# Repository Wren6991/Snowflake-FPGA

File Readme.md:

Snowflake FPGA HAT
==================

As an experiment, I am designing a PCB using only my Pi 4 4GB. Any other machine is off-limits. This includes

- Schematic entry
- Layout
- Datasheets and reference material
- Background Twitter browsing
- Rendering PCB glamour shots:

This is a HAT (Raspberry Pi addon board) with an iCE40 HX8k FPGA. The Pi can program the FPGA, and communicate with it via a UART, or a fast, bidirectional SDIO link. This project was spurred by the realisation that Pi 4 is a plausible FPGA development platform: faster processors, expanded memory and, above all, dramatic improvements in [Symbiotic EDA](https://www.symbioticeda.com/)'s open source design flows in the last few years.

[View schematic (PDF)](board/fpga_hat.pdf)

With the exception of the `datasheet/` directory (to which I do not lay claim), this repository is distributed under the [Apache-2.0 License](License).

Features
--------

- iCE40 HX8k
- 4 Mbit SRAM 16 bit wide, 10 ns access
- 4 Mbit flash for FPGA image and user data; dual I/O support
- 3 PMOD-compatible expansion headers
    - 8 3.3V IOs each, plus power and ground
    - 2 headers on one side, 1 on another; the two on one side have standard 0.9" spacing, allowing use of dual-PMOD boards
- Communication with host Pi:
    - UART
    - SPI for flash programming
    - SDIO for fast communications
    - FPGA reset, and configuration status (CDONE)
- 8 user pushbuttons and LEDs
- Reset button and configuration status LED
- Audio output via 3.5 mm jack (same audio circuit as Pi)

Tolerances
----------

Of the 121 balls on the FPGA's BGA package, I am using 120; the sole unconnected ball is VPP_FAST, which is used only for NVCM programming. This will make the layout exceptionally tight, which is part of the experiment! For a fighting chance, I am using JLCPCB to manufacture the prototype boards, rather than my usual iTead. Their tighter manufacturing tolerances should permit two traces between 0.3 mm pads on a 0.8 mm-pitch BGA, which allows the first 3 ranks of balls to be routed out on layer 1.

The capability requirements for this board are:

- Via drill 0.2 mm
- Via diameter 0.45 mm
- Copper min width 0.09 mm
- Copper-copper clearance 0.09 mm
- Solder mask expansion 0.05 mm

Stackup
-------

This is a 4-layer board.

- L1: signal, GND fill
- L2: GND plane
- L3: Power polygons (+5V, +3V3, +1V2)
- L4: signal, GND fill

All layers 1 oz/sqft copper. Assumed stacking for FR4 layers:

- L1-L2 0.2 mm prepreg
- L2-L3 1.2 mm core
- L3-L4 0.2 mm prepreg

These dimensions are not critical. Signal integrity will be improved by minimising separation of L1-L2, but none of the routing is impedance-controlled.

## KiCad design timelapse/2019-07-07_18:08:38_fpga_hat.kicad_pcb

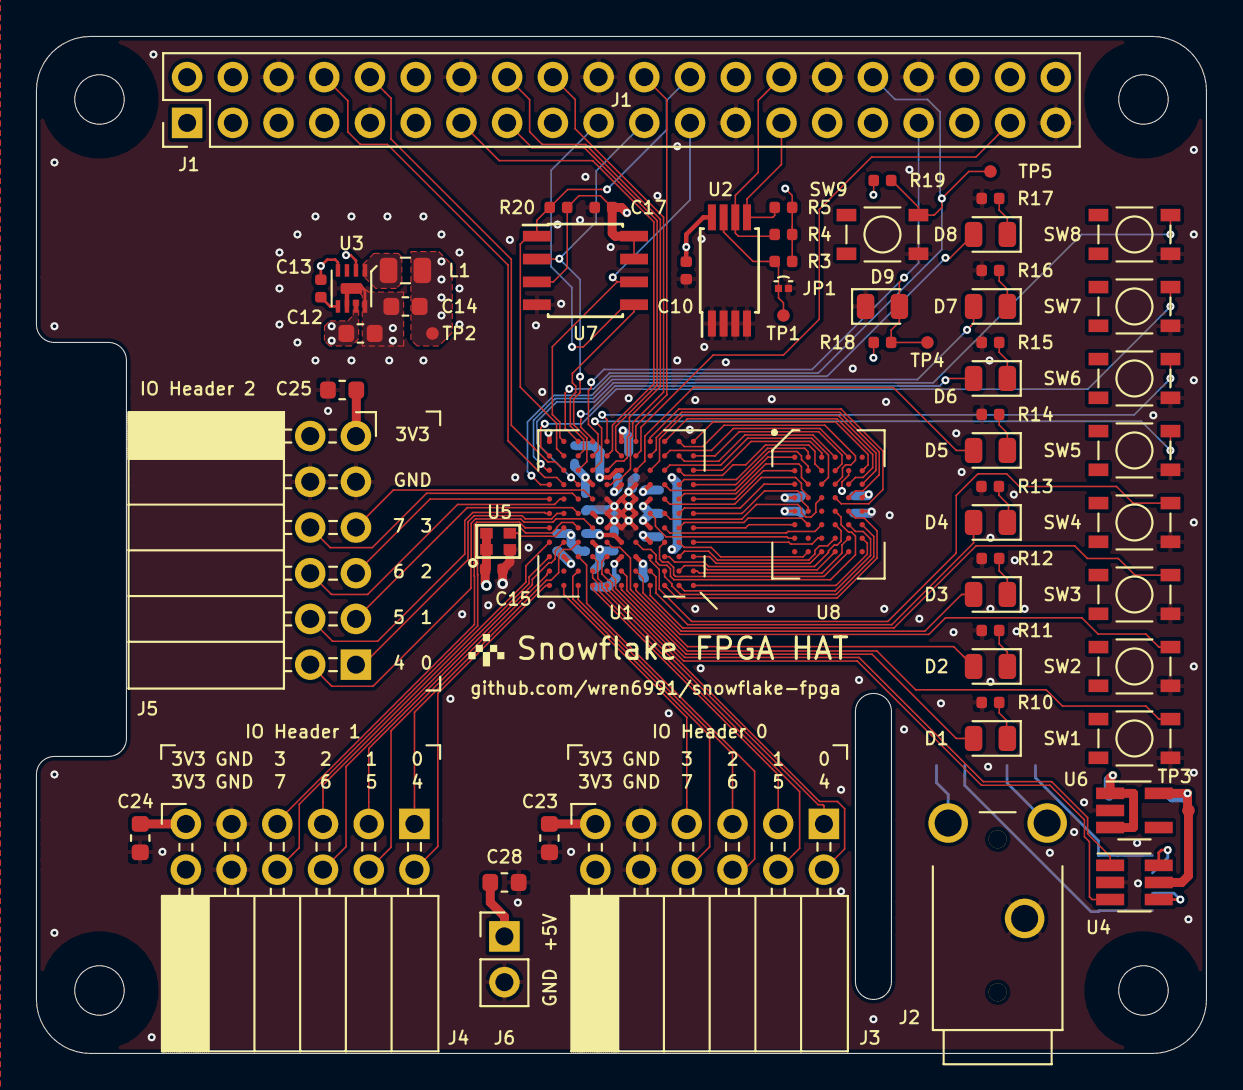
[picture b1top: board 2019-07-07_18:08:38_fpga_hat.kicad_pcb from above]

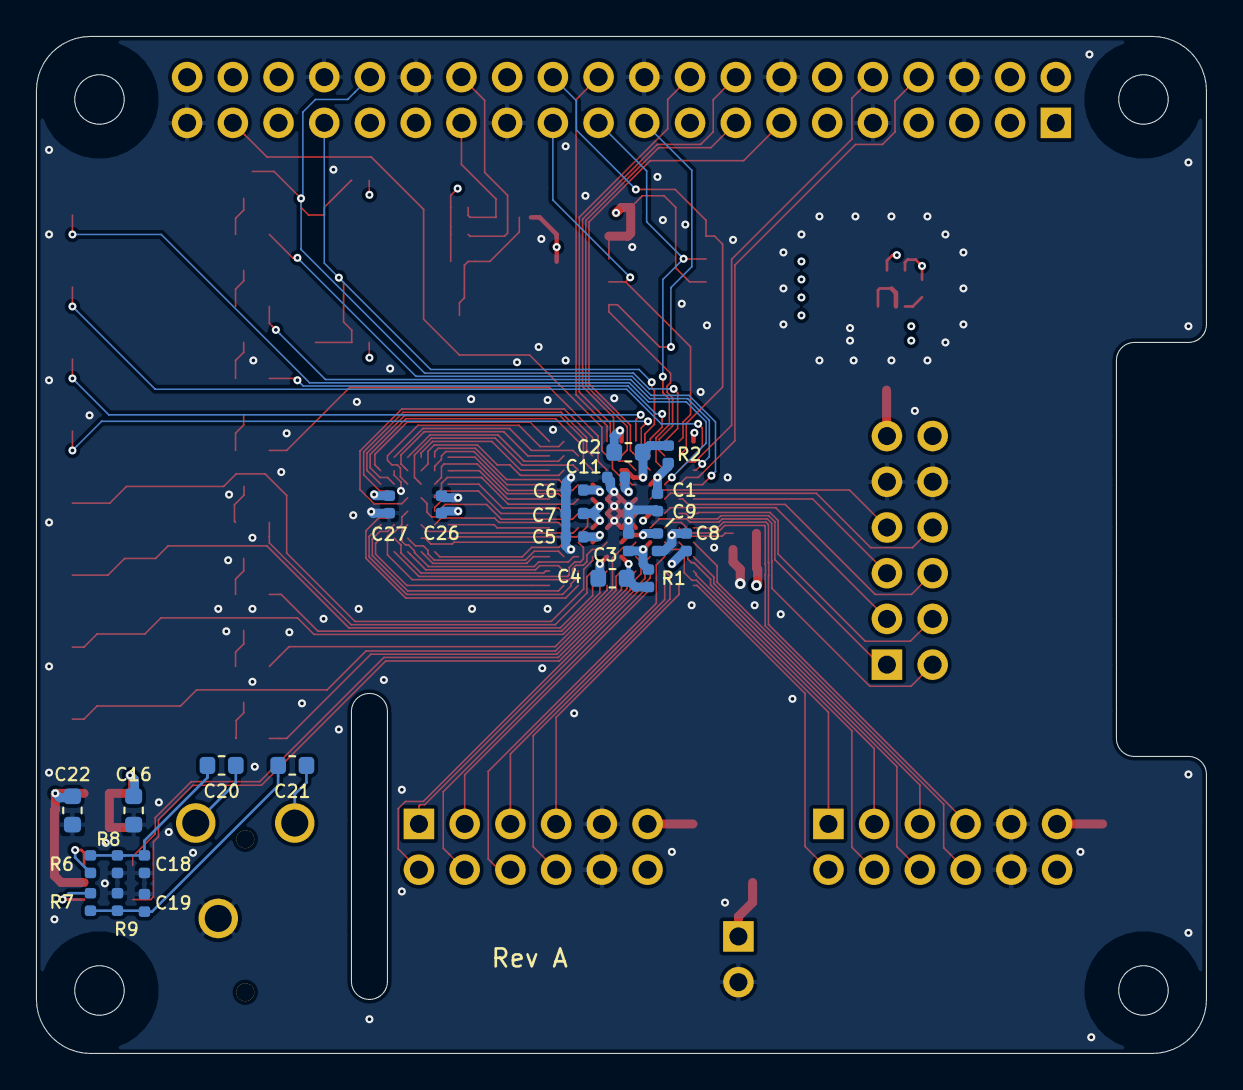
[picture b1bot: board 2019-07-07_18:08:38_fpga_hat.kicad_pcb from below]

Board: 4 copper layers, 65.0 x 56.5 mm, 87 parts (24 on the bottom side), 123 nets.

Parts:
C1, C3, C5, C6, C7, C8, C9, C10, C11, C15, C17, C18, C19, C26, C27: 100n; C_0402_1005Metric
C2, C4, C12, C14, C20, C21: 4u7; C_0603_1608Metric
C13: 560p; C_0402_1005Metric
C16, C22, C23, C24, C25, C28: 1u; C_0603_1608Metric
D1, D2, D3, D4, D5, D6, D7, D8, D9: LED; LED_0805_2012Metric
J1: 2x20; PinHeader_2x20_P2.54mm_Vertical
J2: AudioJack3; STX-3000_TRS_3.5mm
J3, J4, J5: Conn_02x06_Top_Bottom; PinSocket_2x06_P2.54mm_Horizontal
J6: Conn_01x02; PinHeader_1x02_P2.54mm_Vertical
JP1: Solder jumper; SOLDER_JUMP
L1: 1u; L_0805_2012Metric
R1, R2, R8, R9: 100; R_0402_1005Metric
R3, R10, R11, R12, R13, R14, R15, R16, R17, R18: 470; R_0402_1005Metric
R4, R5, R19, R20: 4k7; R_0402_1005Metric
R6, R7: 220; R_0402_1005Metric
SW1, SW2, SW3, SW4, SW5, SW6, SW7, SW8, SW9: PTS815
TP1, TP2, TP3, TP4, TP5: TestPoint; Testpoint_d0.7mm
U1: iCE40-HX8k-BG121; BGA-121_11x11_9.0x9.0mm
U2: CAT24C32WI; TSSOP-8_4.4x3mm_P0.65mm
U3: MIC23050-4YML; DFN8_2x2_0.5mm
U4: 74LVC2G07; SOT-23-6_Handsoldering
U5: DSC60XX; LGA4_1.6x1.2mm
U6: NCP115ASN330T; SOT-23-5_HandSoldering
U7: W25X40CL; SOIC-8_3.9x4.9mm_P1.27mm
U8: IS61WV25616; BGA-48_6x8_6.0x8.0mm

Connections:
+1V2: C1.1, C3.1, C5.1, C6.1, C13.1, C14.1, L1.2, R1.2, R2.2, TP2.1, U1.D4, U1.D8, U1.H4, U1.H8, U3.4
+3.3VDAC: C22.1, TP3.1, U4.5, U6.5
+3V3: C7.1, C8.1, C9.1, C10.1, C11.1, C15.1, C17.1, C23.1, C24.1, C25.1, C26.1, C27.1, J1.1, J1.17, J3.6, J3.12, J4.6, J4.12, J5.6, J5.12, R3.1, R4.1, R5.1, R18.2, R19.1, R20.1, U1.C10, U1.D6, U1.E4, U1.F8, U1.G4, U1.H6, U1.L11, U2.8, U5.1, U5.4, U7.3, U7.7, U7.8, U8.D6, U8.E1
+5V: C12.1, C16.1, C28.1, J1.2, J1.4, J6.1, U3.2, U3.7, U6.1, U6.3
/AUDIO_L_PWM: U1.B7, U4.1
/AUDIO_R_PWM: U1.C7, U4.3
/CLK_OSC: U1.E10, U5.3
/GP8_SPI_~CS: J1.24, R20.2, U1.K10, U7.1
/GP9_SPI_MISO: J1.21, U1.J9, U7.2
/GP10_SPI_MOSI: J1.19, U1.K9, U7.5
/GP11_SPI_SCK: J1.23, U1.L10, U7.6
/GP12_FPGA_~RST: J1.32, R19.2, SW9.1, TP5.1, U1.L9
/GP13_FPGA_CDONE: D9.2, J1.33, R18.1, TP4.1, U1.K8
/GP14_UART_TXD: J1.8, U1.H10
/GP15_UART_RXD: J1.10, U1.J10
/GP22_SDIO_CLK: J1.15, U1.K6
/GP23_SDIO_CMD: J1.16, U1.J7
/GP24_SDIO_DAT0: J1.18, U1.H7
/GP25_SDIO_DAT1: J1.22, U1.L5
/GP26_SDIO_DAT2: J1.37, U1.K5
/GP27_SDIO_DAT3: J1.13, U1.K7
/ID_SC: J1.28, R4.2, U2.6
/ID_SD: J1.27, R5.2, U2.5
/IO0_0: J3.1, U1.C8
/IO0_1: J3.2, U1.A8
/IO0_2: J3.3, U1.A9
/IO0_3: J3.4, U1.A10
/IO0_4: J3.7, U1.A7
/IO0_5: J3.8, U1.B8
/IO0_6: J3.9, U1.C9
/IO0_7: J3.10, U1.B9
/IO1_0: J4.1, U1.D9
/IO1_1: J4.2, U1.D10
/IO1_2: J4.3, U1.D11
/IO1_3: J4.4, U1.E11
/IO1_4: J4.7, U1.A11
/IO1_5: J4.8, U1.B11
/IO1_6: J4.9, U1.C11
/IO1_7: J4.10, U1.E9
/IO2_0: J5.1, U1.F10
/IO2_1: J5.2, U1.F9
/IO2_2: J5.3, U1.G11
/IO2_3: J5.4, U1.G8
/IO2_4: J5.7, U1.E8
/IO2_5: J5.8, U1.F11
/IO2_6: J5.9, U1.G10
/IO2_7: J5.10, U1.G9
/LED0: D1.2, U1.A6
/LED1: D2.2, U1.D7
/LED2: D3.2, U1.B5
/LED3: D4.2, U1.B4
/LED4: D5.2, U1.J5
/LED5: D6.2, U1.L8
/LED6: D7.2, U1.J11
/LED7: D8.2, U1.H11
/SRAM_A0: U1.J1, U8.A3
/SRAM_A1: U1.K2, U8.A4
/SRAM_A2: U1.K3, U8.A5
/SRAM_A3: U1.J2, U8.B3
/SRAM_A4: U1.K1, U8.B4
/SRAM_A5: U1.J3, U8.C3
/SRAM_A6: U1.L2, U8.C4
/SRAM_A7: U1.L4, U8.D4
/SRAM_A8: U1.D2, U8.H2
/SRAM_A9: U1.C1, U8.H3
/SRAM_A10: U1.B2, U8.H4
/SRAM_A11: U1.D3, U8.H5
/SRAM_A12: U1.D1, U8.G3
/SRAM_A13: U1.C2, U8.G4
/SRAM_A14: U1.E3, U8.F3
/SRAM_A15: U1.C3, U8.F4
/SRAM_A16: U1.D5, U8.E4
/SRAM_A17: U1.F3, U8.D3
/SRAM_DQ0: U1.L1, U8.B6
/SRAM_DQ1: U1.L3, U8.C5
/SRAM_DQ2: U1.J4, U8.C6
/SRAM_DQ3: U1.K4, U8.D5
/SRAM_DQ4: U1.A3, U8.E5
/SRAM_DQ5: U1.A2, U8.F5
/SRAM_DQ6: U1.B3, U8.F6
/SRAM_DQ7: U1.A1, U8.G6
/SRAM_DQ8: U1.G1, U8.B1
/SRAM_DQ9: U1.F2, U8.C1
/SRAM_DQ10: U1.G2, U8.C2
/SRAM_DQ11: U1.G3, U8.D2
/SRAM_DQ12: U1.F1, U8.E2
/SRAM_DQ13: U1.E2, U8.F2
/SRAM_DQ14: U1.E1, U8.F1
/SRAM_DQ15: U1.F4, U8.G1
/SRAM_~LB: U1.H3, U8.A1
/SRAM_~OE: U1.H2, U8.A2
/SRAM_~UB: U1.H1, U8.B2
/SRAM_~WE: U1.B1, U8.G5
/SW0: SW1.1, U1.B6
/SW1: SW2.1, U1.A5
/SW2: SW3.1, U1.A4
/SW3: SW4.1, U1.C4
/SW4: SW5.1, U1.J8
/SW5: SW6.1, U1.L7
/SW6: SW7.1, U1.K11
/SW7: SW8.1, U1.H9
GND: C1.2, C3.2, C5.2, C6.2, C7.2, C8.2, C9.2, C10.2, C11.2, C12.2, C14.2, C15.2, C16.2, C17.2, C18.2, C19.2, C22.2, C23.2, C24.2, C25.2, C26.2, C27.2, C28.2, D9.1, J1.6, J1.9, J1.14, J1.20, J1.25, J1.30, J1.34, J1.39, J2.S, J3.5, J3.11, J4.5, J4.11, J5.5, J5.11, J6.2, JP1.2, R8.2, R9.2, R10.1, R11.1, R12.1, R13.1, R14.1, R15.1, R16.1, R17.1, SW1.2, SW2.2, SW3.2, SW4.2, SW5.2, SW6.2, SW7.2, SW8.2, SW9.2, U1.E5, U1.E6, U1.E7, U1.F5, U1.F6, U1.F7, U1.G5, U1.G6, U1.G7, U1.H5, U2.1, U2.2, U2.3, U2.4, U3.6, U3.8, U4.2, U5.2, U6.2, U7.4, U8.B5, U8.D1, U8.E6
unnamed: C2.1, R2.1, U1.J6
unnamed: C2.2, U1.L6
unnamed: C4.1, R1.1, U1.C6
unnamed: C4.2, U1.C5
unnamed: C13.2, U3.5
unnamed: C18.1, C20.2, R6.1, R8.1
unnamed: C19.1, C21.2, R7.1, R9.1
unnamed: C20.1, J2.T
unnamed: C21.1, J2.R
unnamed: D1.1, R10.2
unnamed: D2.1, R11.2
unnamed: D3.1, R12.2
unnamed: D4.1, R13.2
unnamed: D5.1, R14.2
unnamed: D6.1, R15.2
unnamed: D7.1, R16.2
unnamed: D8.1, R17.2
unnamed: JP1.1, R3.2, TP1.1, U2.7
unnamed: L1.1, U3.1
unnamed: R6.2, U4.6
unnamed: R7.2, U4.4

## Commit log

2019-06-29 Probably time for another commit :)
2019-06-29 Add SRAM BGA footprint, and add it to schematic
2019-06-29 Add switches and LEDs
2019-06-30 Add datasheet for SRAM, core regulator. Add core regulator to schematic. Some tidy-up.
2019-06-30 Add more datasheets. Add FPGA decoupling. Add button + LED for FPGA RST/CDONE
2019-06-30 Add config flash, fix some ERC errors
2019-06-30 Review schematic and symbols against datasheets; minor corrections. ERC is now clean.
2019-06-30 Add footprints for FPGA, SRAM, SMPS. Do some footprint association.
2019-06-30 More footprints
2019-07-01 Footprints 100%
2019-07-01 Add Readme and schematic PDF
2019-07-01 Board outline, mounting holes, slot
2019-07-01 Add new footprint for PMOD connectors, with correct pin numbering
2019-07-01 Add footprint for new, smaller tact switch. Add some datasheets
2019-07-02 Add 5V header to schematic -- useful for some PMODs. Move camera slot 1.5mm to right, to leave room for PMODs.
2019-07-02 Add watch script for timelapse
2019-07-02 Start placing components
2019-07-02 All parts on board
2019-07-02 First run at power planes under FPGA
2019-07-02 Nobody cares about your return code inotify
2019-07-02 Start BGA escape
2019-07-02 Continue FPGA escape. Start escaping SRAM.
2019-07-02 SRAM escaped. Some work on FPGA power routing. Some SRAM pinswapping.
2019-07-02 More FPGA escape
2019-07-03 Continue BGA route-out. SRAM connected, start heading out toward LEDs and IO.
2019-07-03 Continue routing
2019-07-05 Connect up SDIO, remaining buttons + LEDs.
2019-07-06 Start fixing up planes
2019-07-06 Routed 100%
2019-07-06 Clean up minor DRC
2019-07-06 Tidy up L1 silkscreen
2019-07-06 Tidy up both silkscreen layers. Remove copper from mounting hole screw lands.
2019-07-07 Add pinout on silkscreen, move TP5
2019-07-07 Tidy up SRAM escape and decoupling
2019-07-07 Re-render PDF schematic
2019-07-07 Update readme, add license
2019-07-07 Fix small silkscreen error, improve ground stitching and core supply layout
2019-07-07 Rename board. Some silkscreen tweaks.
2019-07-07 Move core VDD enable to +3V3 to improve power supply staging
2019-07-07 Add stackup information to readme
